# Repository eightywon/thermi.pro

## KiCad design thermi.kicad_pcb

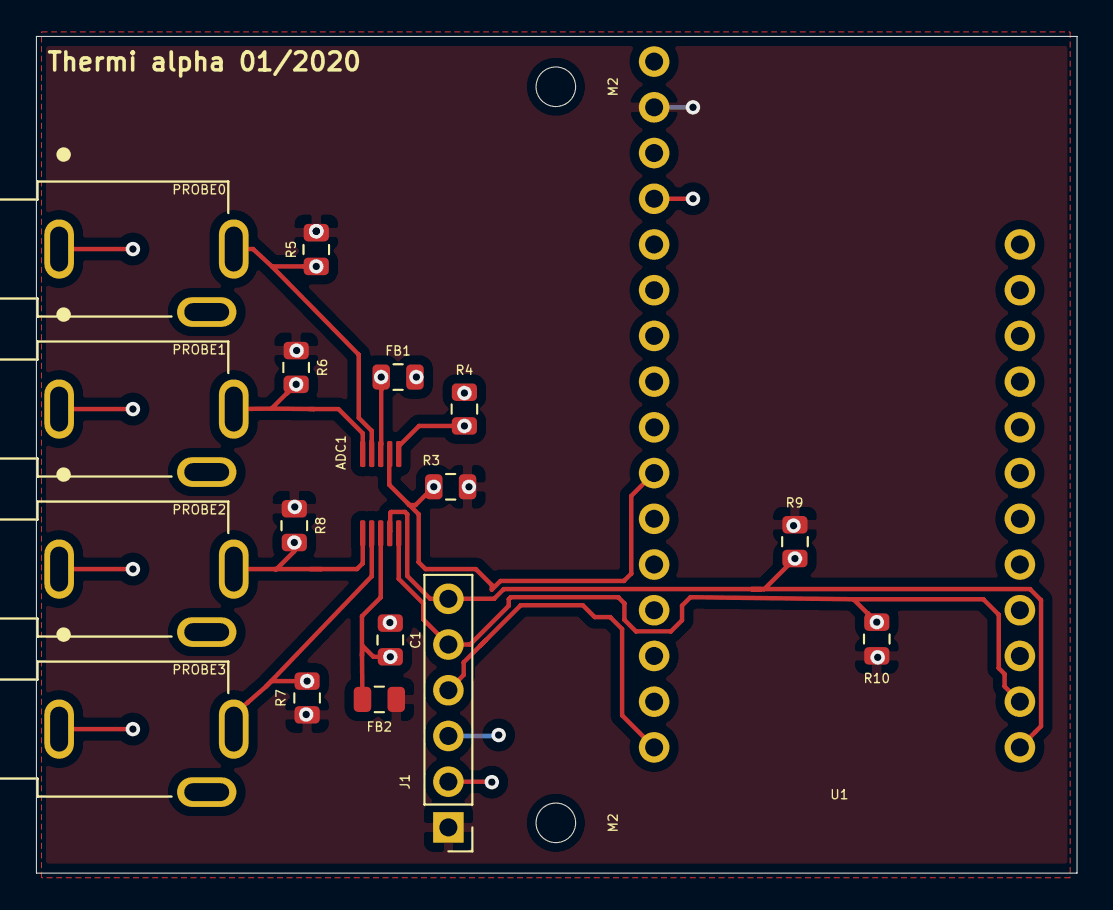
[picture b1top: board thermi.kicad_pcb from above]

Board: 2 copper layers, 57.8 x 46.5 mm, 20 parts (0 on the bottom side), 13 nets.

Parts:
ADC1: ADS1115IDGST; VSSOP-10_3x3mm_P0.5mm
C1: 1uf; C_0805_2012Metric
FB1, FB2: MMZ2012Y152B; R_0805_2012Metric
J1: Conn_01x06_Male; PinHeader_1x06_P2.54mm_Vertical
M2, M2#2: MountingHole_2.2mm_M2
PROBE0, PROBE1, PROBE2, PROBE3: MJ-2508; CUI_MJ-2508
R3, R4, R5, R6, R7, R8, R9, R10: 10k; R_0805_2012Metric
U1: ESP32_HUZZAH

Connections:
GND: C1.2, FB1.1, J1.3, PROBE0.1, PROBE1.1, PROBE2.1, PROBE3.1, R4.1, U1.4
unnamed: ADC1.1, R4.2
unnamed: ADC1.2, R3.2, U1.10
unnamed: ADC1.3, FB1.2
unnamed: ADC1.4, PROBE0.2, R5.2
unnamed: ADC1.5, PROBE1.2, R6.2
unnamed: ADC1.6, PROBE2.2, R8.2
unnamed: ADC1.7, PROBE3.2, R7.2
unnamed: ADC1.8, C1.1, FB2.2
unnamed: ADC1.9, J1.6, R9.2, U1.28
unnamed: ADC1.10, J1.5, R10.2, U1.27
unnamed: J1.4, U1.16
VDD: FB2.1, J1.1, R3.1, R5.1, R6.1, R7.1, R8.1, R9.1, R10.1, U1.2

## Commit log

2020-01-23 0.0.1
